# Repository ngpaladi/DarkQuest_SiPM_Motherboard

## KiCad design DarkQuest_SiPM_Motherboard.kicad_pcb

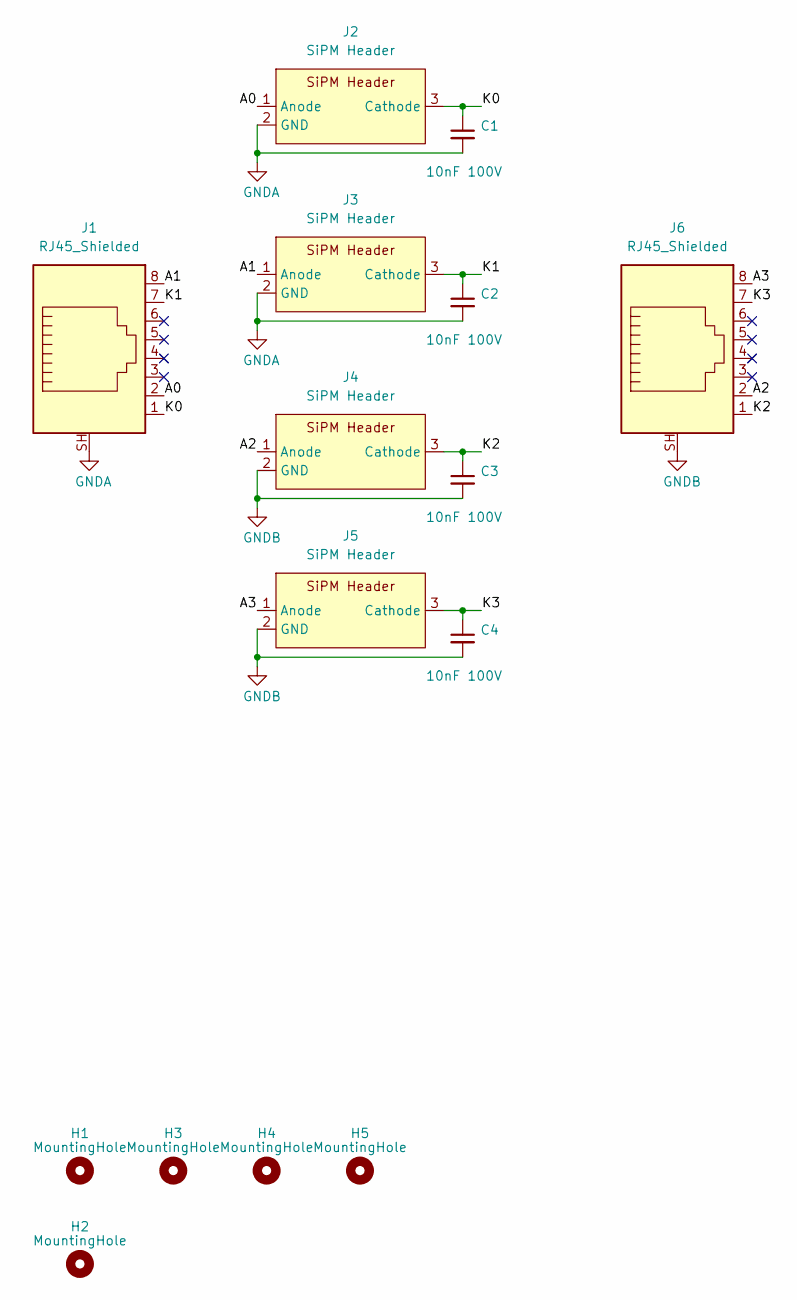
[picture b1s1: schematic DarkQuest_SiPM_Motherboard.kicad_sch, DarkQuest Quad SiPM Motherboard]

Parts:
C1, C2, C3, C4: 10nF 100V; C_1206_3216Metric_Pad1.33x1.80mm_HandSolder; DigiKey 399-17911-1-ND
H1, H3, H4, H5: MountingHole; MountingHole_6.4_pad
H2: MountingHole; MountingHole_8.4mm_M8_Pad
J1, J6: RJ45_Shielded; RJJS-88-122-E7V-022
J2, J3, J4, J5: SiPM Header; chip_carrier_pin_header

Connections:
/A0: J1.2, J2.1 (Anode)
/A1: J1.8, J3.1 (Anode)
/A2: J4.1 (Anode), J6.2
/A3: J5.1 (Anode), J6.8
/K0: C1.1, J1.1, J2.3 (Cathode)
/K1: C2.1, J1.7, J3.3 (Cathode)
/K2: C3.1, J4.3 (Cathode), J6.1
/K3: C4.1, J5.3 (Cathode), J6.7
GNDA: C1.2, C2.2, J1.SH, J2.2 (GND), J3.2 (GND)
GNDB: C3.2, C4.2, J4.2 (GND), J5.2 (GND), J6.SH

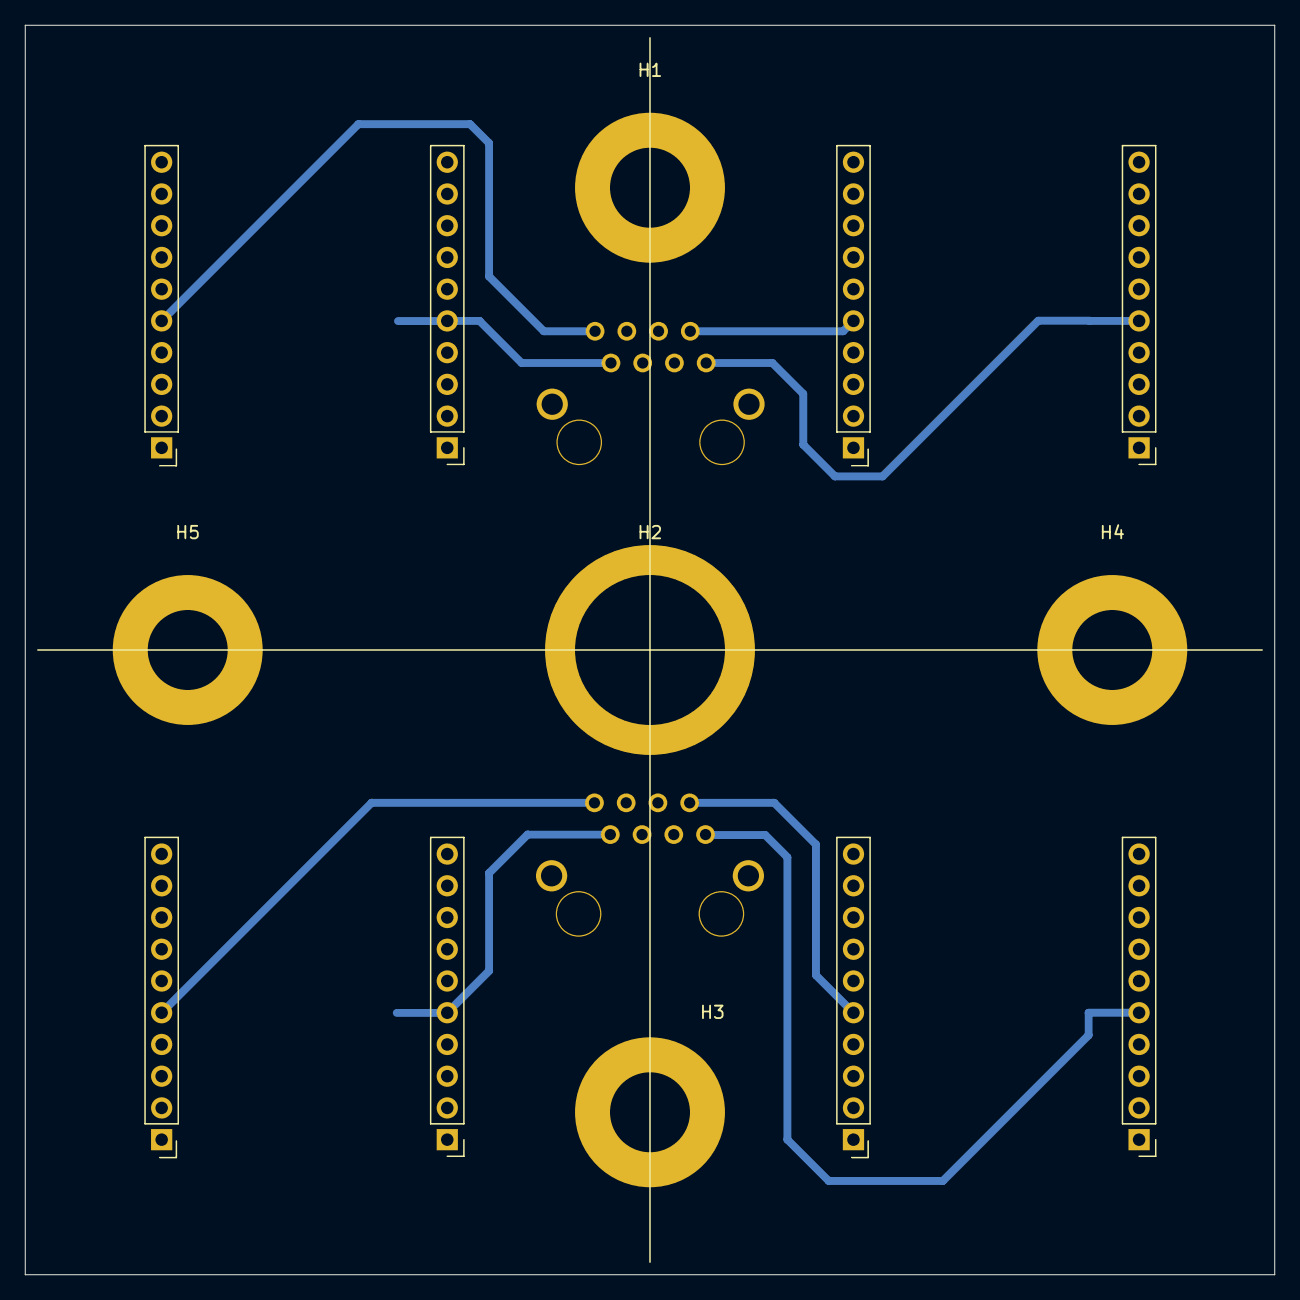
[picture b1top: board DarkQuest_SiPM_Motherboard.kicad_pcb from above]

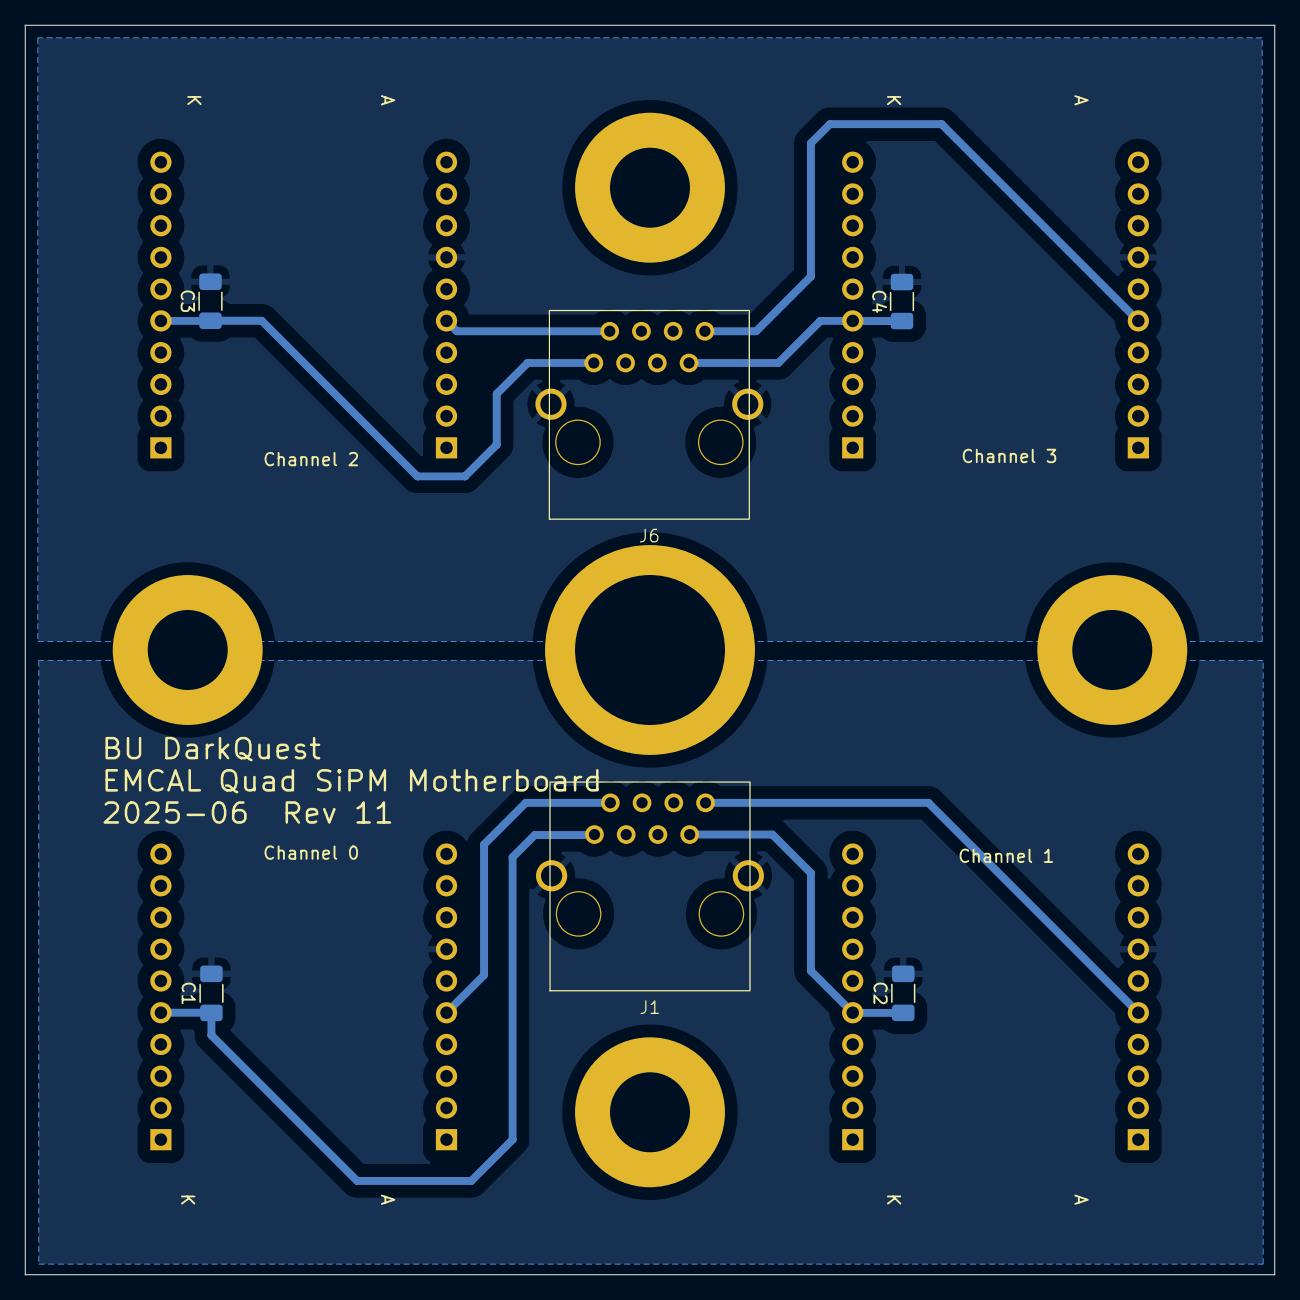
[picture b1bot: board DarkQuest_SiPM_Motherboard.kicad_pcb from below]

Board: 2 copper layers, 100.0 x 100.0 mm, 15 parts (6 on the bottom side), 10 nets.

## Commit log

2025-05-21 RJ45v10
2025-05-29 Added HDMI option
2025-06-11 Added stencil
2025-06-12 Finished initial routing
2025-06-13 Clean up output
2025-06-24 Dual RJ45 Solution
